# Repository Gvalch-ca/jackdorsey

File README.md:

# Lumberjerk keyboard by Gvalch'ca

The design is inspired by Lumberjack PCB. It is designed by peej and available at this repo:
https://github.com/peej/lumberjack-keyboard/

## About the PCB

Lumberjerk is designed for Alps SKCL/SKCM and NMB Hi-Tek 725 "Space Invaders" switches. It is a 6x5 "split" with exposed components in between the halves.

Form-factor of the PCB is standard 60% (GH60-compatible). Two middle posts are removed though (but who cares?). Also the posts between Tab & Q and ] & \ are partially covered with the switches and it might be difficult to screw them. If you use SI switches, you'll also need to remove one switch leg in order to use these posts.

The PCB is designed to be used with BLE pro-micro compatible controller (e.g. nice!nano). Wired controller could be used too. In this case you'll need to solder JST connector and USB mini B (bottom mount) and connect your controller to the internal JST.

Also, there is second JST connector on the bottom of the board. It is meant to be used with daughterboard. OFC it requires you to use the same method with internal USB->JST cable.

## Build guide
TBD

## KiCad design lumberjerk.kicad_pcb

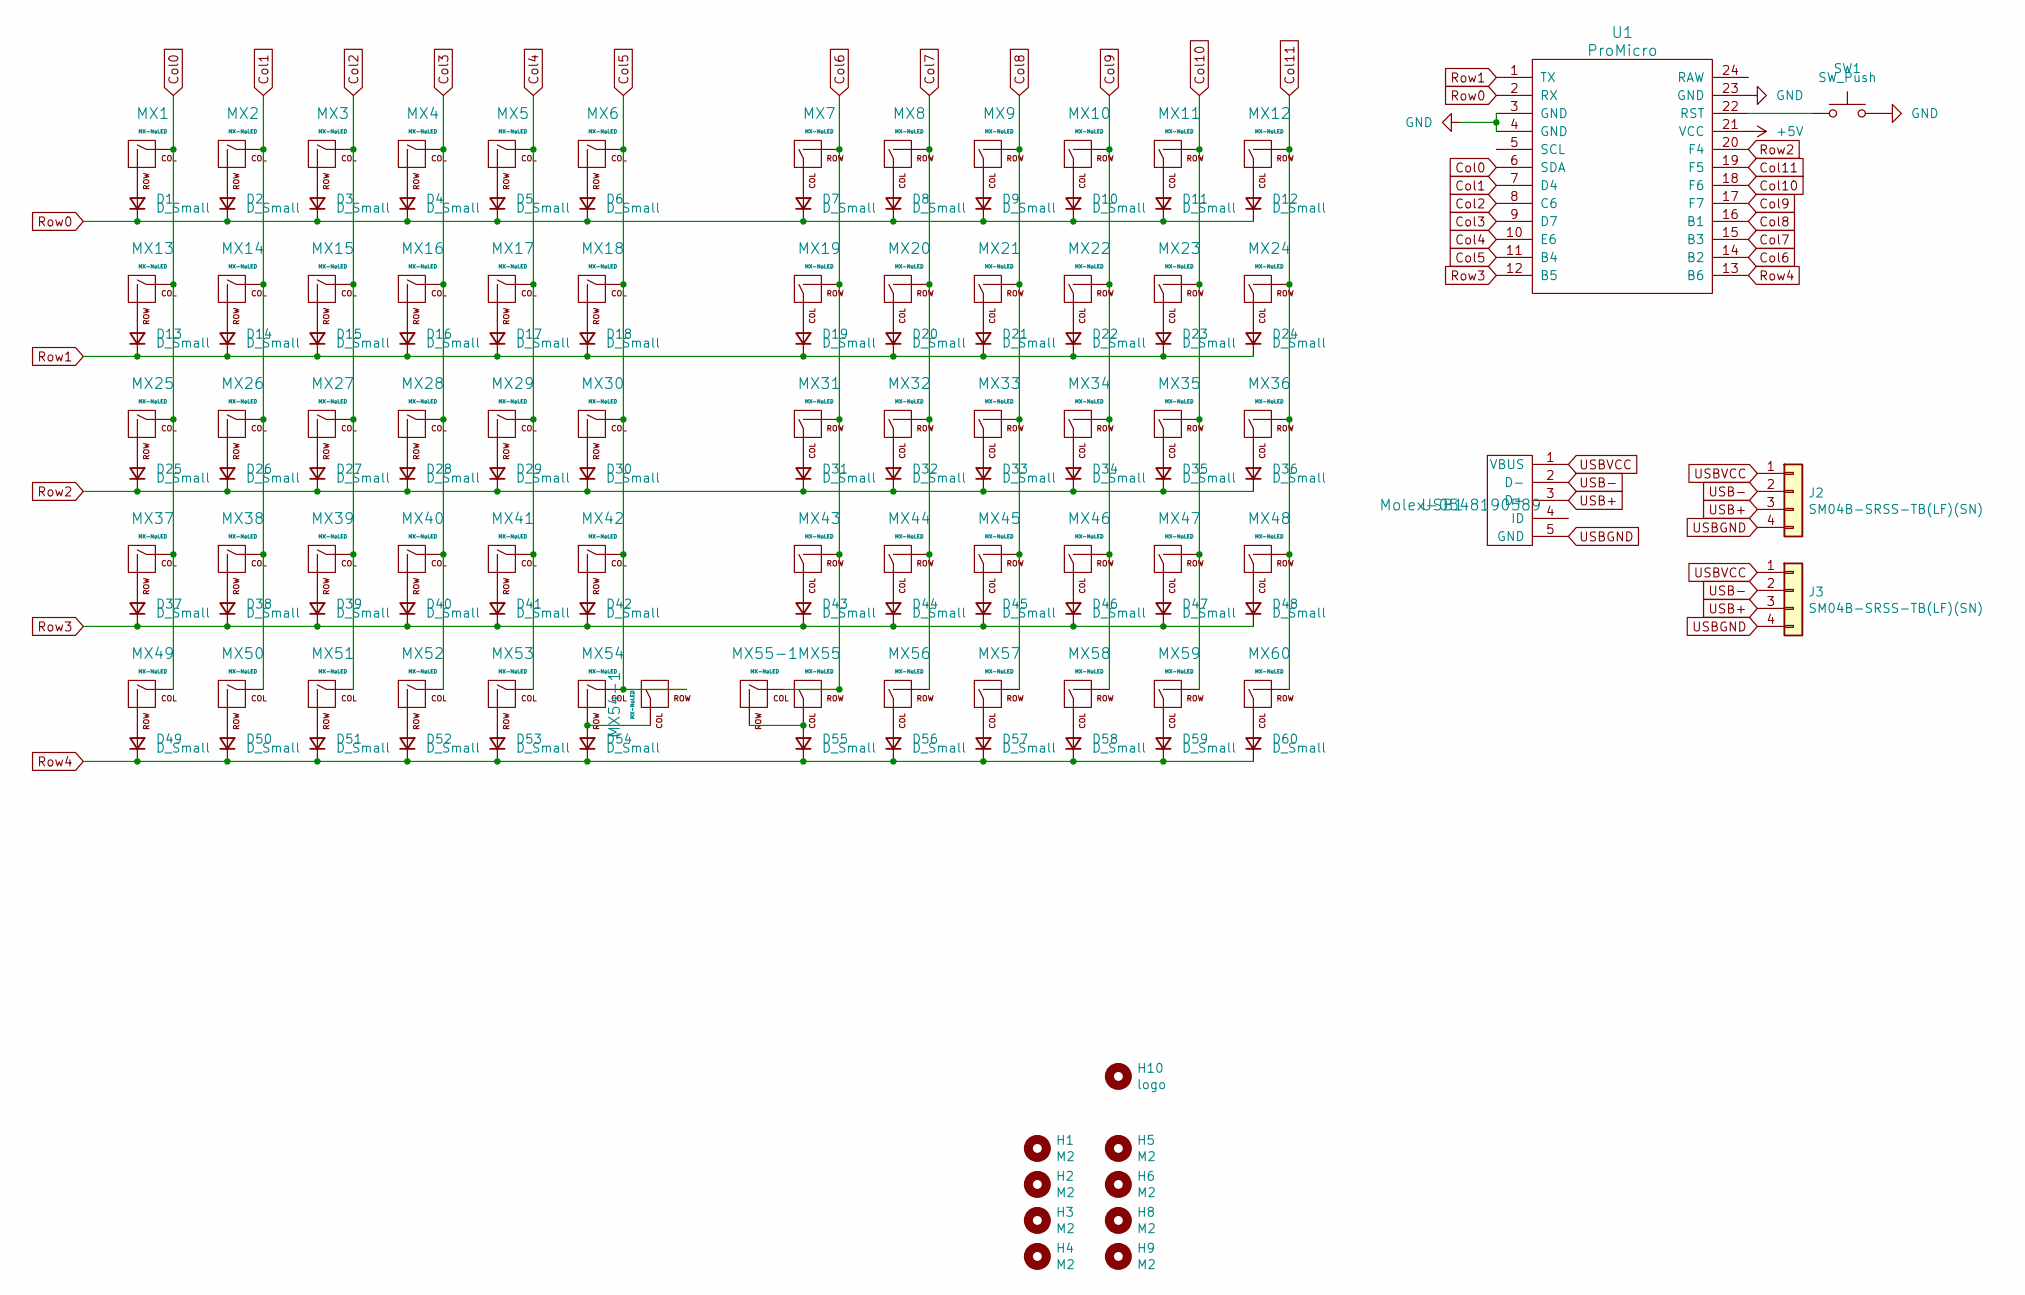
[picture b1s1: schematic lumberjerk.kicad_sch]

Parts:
D1, D2, D3, D4, D5, D6, D7, D8, D9, D10, D11, D12, D13, D14, D15, D16, D17, D18, D19, D20, D21, D22, D23, D24, D25, D26, D27, D28, D29, D30, D31, D32, D33, D34, D35, D36, D37, D38, D39, D40, D41, D42, D43, D44, D45, D46, D47, D48, D49, D50, D51, D52, D53, D54, D55, D56, D57, D58, D59, D60: D_Small; D_SOD-123
H1, H2, H3, H4: M2; MountingHole_M2
H5, H6: M2; poker-screw-wide
H8, H9: M2; poker-screw-normal
H10: logo; falcon
J2, J3: SM04B-SRSS-TB(LF)(SN); JST-SR-4; Manufacturer Part No SM04B-SRSS-TB(LF)(SN); LCSC Part No C160404
MX1, MX2, MX3, MX4, MX5, MX6, MX7, MX8, MX9, MX10, MX11, MX12, MX13, MX14, MX15, MX16, MX17, MX18, MX19, MX20, MX21, MX22, MX23, MX24, MX25, MX26, MX27, MX28, MX29, MX30, MX31, MX32, MX33, MX34, MX35, MX36, MX37, MX38, MX39, MX40, MX41, MX42, MX43, MX44, MX45, MX46, MX47, MX48, MX49, MX50, MX51, MX52, MX53, MX54, MX55, MX56, MX57, MX58, MX59, MX60: MX-NoLED; ALPS-SI-1U
MX54-1, MX55-1: MX-NoLED; ALPS-SI-2U
SW1: SW_Push; Jumper-UserFriendly
U1: ProMicro
USB1: Molex-0548190589; Molex-54819-0519-MFG

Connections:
+5V: U1.21 (VCC)
Col0: MX1.1 (COL), MX13.1 (COL), MX25.1 (COL), MX37.1 (COL), MX49.1 (COL), U1.6 (SDA)
Col1: MX2.1 (COL), MX14.1 (COL), MX26.1 (COL), MX38.1 (COL), MX50.1 (COL), U1.7 (D4)
Col2: MX3.1 (COL), MX15.1 (COL), MX27.1 (COL), MX39.1 (COL), MX51.1 (COL), U1.8 (C6)
Col3: MX4.1 (COL), MX16.1 (COL), MX28.1 (COL), MX40.1 (COL), MX52.1 (COL), U1.9 (D7)
Col4: MX5.1 (COL), MX17.1 (COL), MX29.1 (COL), MX41.1 (COL), MX53.1 (COL), U1.10 (E6)
Col5: MX6.1 (COL), MX18.1 (COL), MX30.1 (COL), MX42.1 (COL), MX54.1 (COL), MX54-1.2 (ROW), U1.11 (B4)
Col6: MX7.2 (ROW), MX19.2 (ROW), MX31.2 (ROW), MX43.2 (ROW), MX55.2 (ROW), MX55-1.1 (COL), U1.14 (B2)
Col7: MX8.2 (ROW), MX20.2 (ROW), MX32.2 (ROW), MX44.2 (ROW), MX56.2 (ROW), U1.15 (B3)
Col8: MX9.2 (ROW), MX21.2 (ROW), MX33.2 (ROW), MX45.2 (ROW), MX57.2 (ROW), U1.16 (B1)
Col9: MX10.2 (ROW), MX22.2 (ROW), MX34.2 (ROW), MX46.2 (ROW), MX58.2 (ROW), U1.17 (F7)
Col10: MX11.2 (ROW), MX23.2 (ROW), MX35.2 (ROW), MX47.2 (ROW), MX59.2 (ROW), U1.18 (F6)
Col11: MX12.2 (ROW), MX24.2 (ROW), MX36.2 (ROW), MX48.2 (ROW), MX60.2 (ROW), U1.19 (F5)
GND: SW1.2, U1.3 (GND), U1.4 (GND), U1.23 (GND)
unnamed: D1.2 (A), MX1.2 (ROW)
unnamed: D2.2 (A), MX2.2 (ROW)
unnamed: D3.2 (A), MX3.2 (ROW)
unnamed: D4.2 (A), MX4.2 (ROW)
unnamed: D5.2 (A), MX5.2 (ROW)
unnamed: D6.2 (A), MX6.2 (ROW)
unnamed: D7.2 (A), MX7.1 (COL)
unnamed: D8.2 (A), MX8.1 (COL)
unnamed: D9.2 (A), MX9.1 (COL)
unnamed: D10.2 (A), MX10.1 (COL)
unnamed: D11.2 (A), MX11.1 (COL)
unnamed: D12.2 (A), MX12.1 (COL)
unnamed: D13.2 (A), MX13.2 (ROW)
unnamed: D14.2 (A), MX14.2 (ROW)
unnamed: D15.2 (A), MX15.2 (ROW)
unnamed: D16.2 (A), MX16.2 (ROW)
unnamed: D17.2 (A), MX17.2 (ROW)
unnamed: D18.2 (A), MX18.2 (ROW)
unnamed: D19.2 (A), MX19.1 (COL)
unnamed: D20.2 (A), MX20.1 (COL)
unnamed: D21.2 (A), MX21.1 (COL)
unnamed: D22.2 (A), MX22.1 (COL)
unnamed: D23.2 (A), MX23.1 (COL)
unnamed: D24.2 (A), MX24.1 (COL)
unnamed: D25.2 (A), MX25.2 (ROW)
unnamed: D26.2 (A), MX26.2 (ROW)
unnamed: D27.2 (A), MX27.2 (ROW)
unnamed: D28.2 (A), MX28.2 (ROW)
unnamed: D29.2 (A), MX29.2 (ROW)
unnamed: D30.2 (A), MX30.2 (ROW)
unnamed: D31.2 (A), MX31.1 (COL)
unnamed: D32.2 (A), MX32.1 (COL)
unnamed: D33.2 (A), MX33.1 (COL)
unnamed: D34.2 (A), MX34.1 (COL)
unnamed: D35.2 (A), MX35.1 (COL)
unnamed: D36.2 (A), MX36.1 (COL)
unnamed: D37.2 (A), MX37.2 (ROW)
unnamed: D38.2 (A), MX38.2 (ROW)
unnamed: D39.2 (A), MX39.2 (ROW)
unnamed: D40.2 (A), MX40.2 (ROW)
unnamed: D41.2 (A), MX41.2 (ROW)
unnamed: D42.2 (A), MX42.2 (ROW)
unnamed: D43.2 (A), MX43.1 (COL)
unnamed: D44.2 (A), MX44.1 (COL)
unnamed: D45.2 (A), MX45.1 (COL)
unnamed: D46.2 (A), MX46.1 (COL)
unnamed: D47.2 (A), MX47.1 (COL)
unnamed: D48.2 (A), MX48.1 (COL)
unnamed: D49.2 (A), MX49.2 (ROW)
unnamed: D50.2 (A), MX50.2 (ROW)
unnamed: D51.2 (A), MX51.2 (ROW)
unnamed: D52.2 (A), MX52.2 (ROW)
unnamed: D53.2 (A), MX53.2 (ROW)
unnamed: D54.2 (A), MX54.2 (ROW), MX54-1.1 (COL)
unnamed: D55.2 (A), MX55.1 (COL), MX55-1.2 (ROW)
unnamed: D56.2 (A), MX56.1 (COL)
unnamed: D57.2 (A), MX57.1 (COL)
unnamed: D58.2 (A), MX58.1 (COL)
unnamed: D59.2 (A), MX59.1 (COL)
unnamed: D60.2 (A), MX60.1 (COL)
unnamed: SW1.1, U1.22 (RST)
Row0: D1.1 (K), D2.1 (K), D3.1 (K), D4.1 (K), D5.1 (K), D6.1 (K), D7.1 (K), D8.1 (K), D9.1 (K), D10.1 (K), D11.1 (K), D12.1 (K), U1.2 (RX)
Row1: D13.1 (K), D14.1 (K), D15.1 (K), D16.1 (K), D17.1 (K), D18.1 (K), D19.1 (K), D20.1 (K), D21.1 (K), D22.1 (K), D23.1 (K), D24.1 (K), U1.1 (TX)
Row2: D25.1 (K), D26.1 (K), D27.1 (K), D28.1 (K), D29.1 (K), D30.1 (K), D31.1 (K), D32.1 (K), D33.1 (K), D34.1 (K), D35.1 (K), D36.1 (K), U1.20 (F4)
Row3: D37.1 (K), D38.1 (K), D39.1 (K), D40.1 (K), D41.1 (K), D42.1 (K), D43.1 (K), D44.1 (K), D45.1 (K), D46.1 (K), D47.1 (K), D48.1 (K), U1.12 (B5)
Row4: D49.1 (K), D50.1 (K), D51.1 (K), D52.1 (K), D53.1 (K), D54.1 (K), D55.1 (K), D56.1 (K), D57.1 (K), D58.1 (K), D59.1 (K), D60.1 (K), U1.13 (B6)
USB+: J2.3, J3.3, USB1.3 (D+)
USB-: J2.2, J3.2, USB1.2 (D-)
USBGND: J2.4, J3.4, USB1.5 (GND)
USBVCC: J2.1, J3.1, USB1.1 (VBUS)

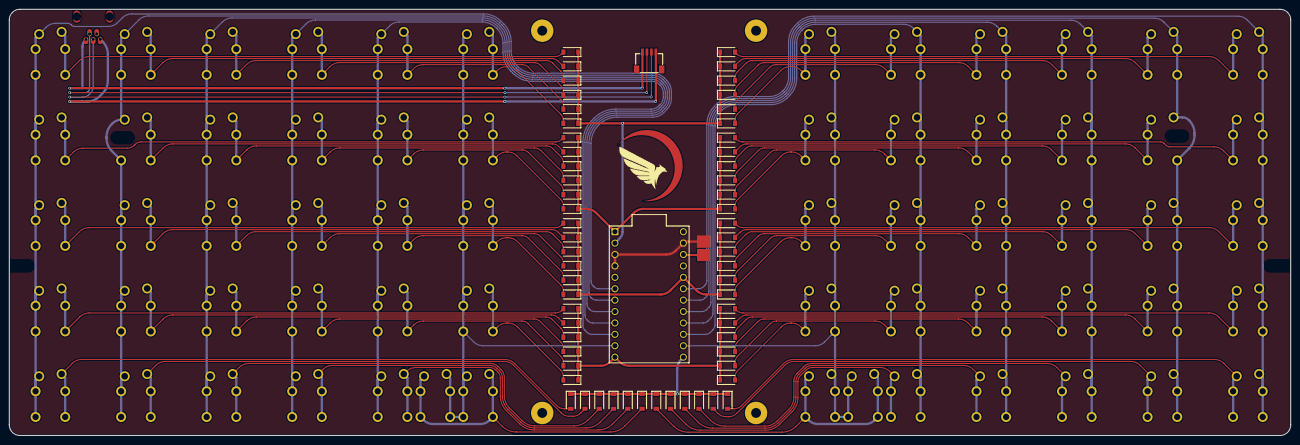
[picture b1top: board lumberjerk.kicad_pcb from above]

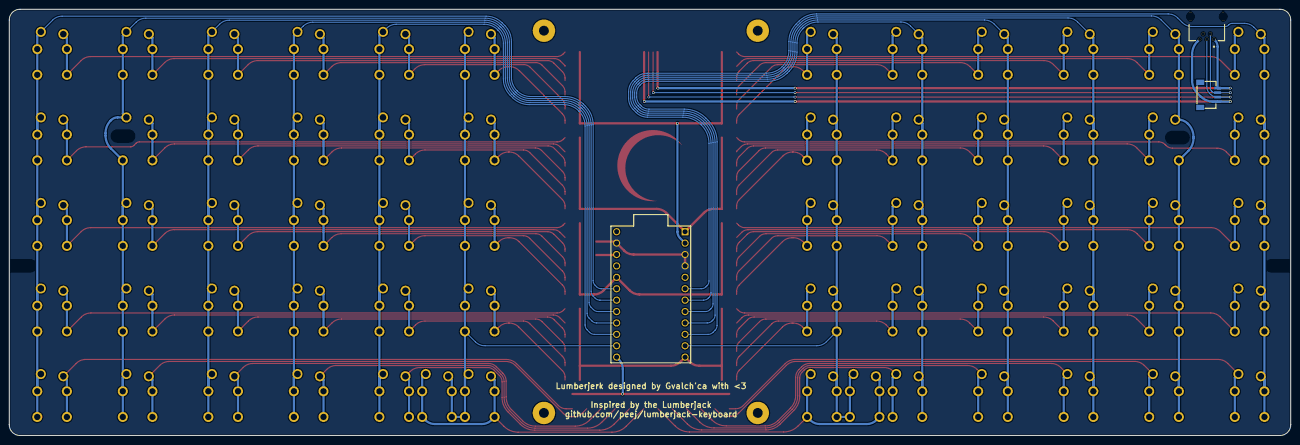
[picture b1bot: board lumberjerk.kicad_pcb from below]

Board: 2 copper layers, 285.4 x 94.9 mm, 136 parts (2 on the bottom side), 83 nets.

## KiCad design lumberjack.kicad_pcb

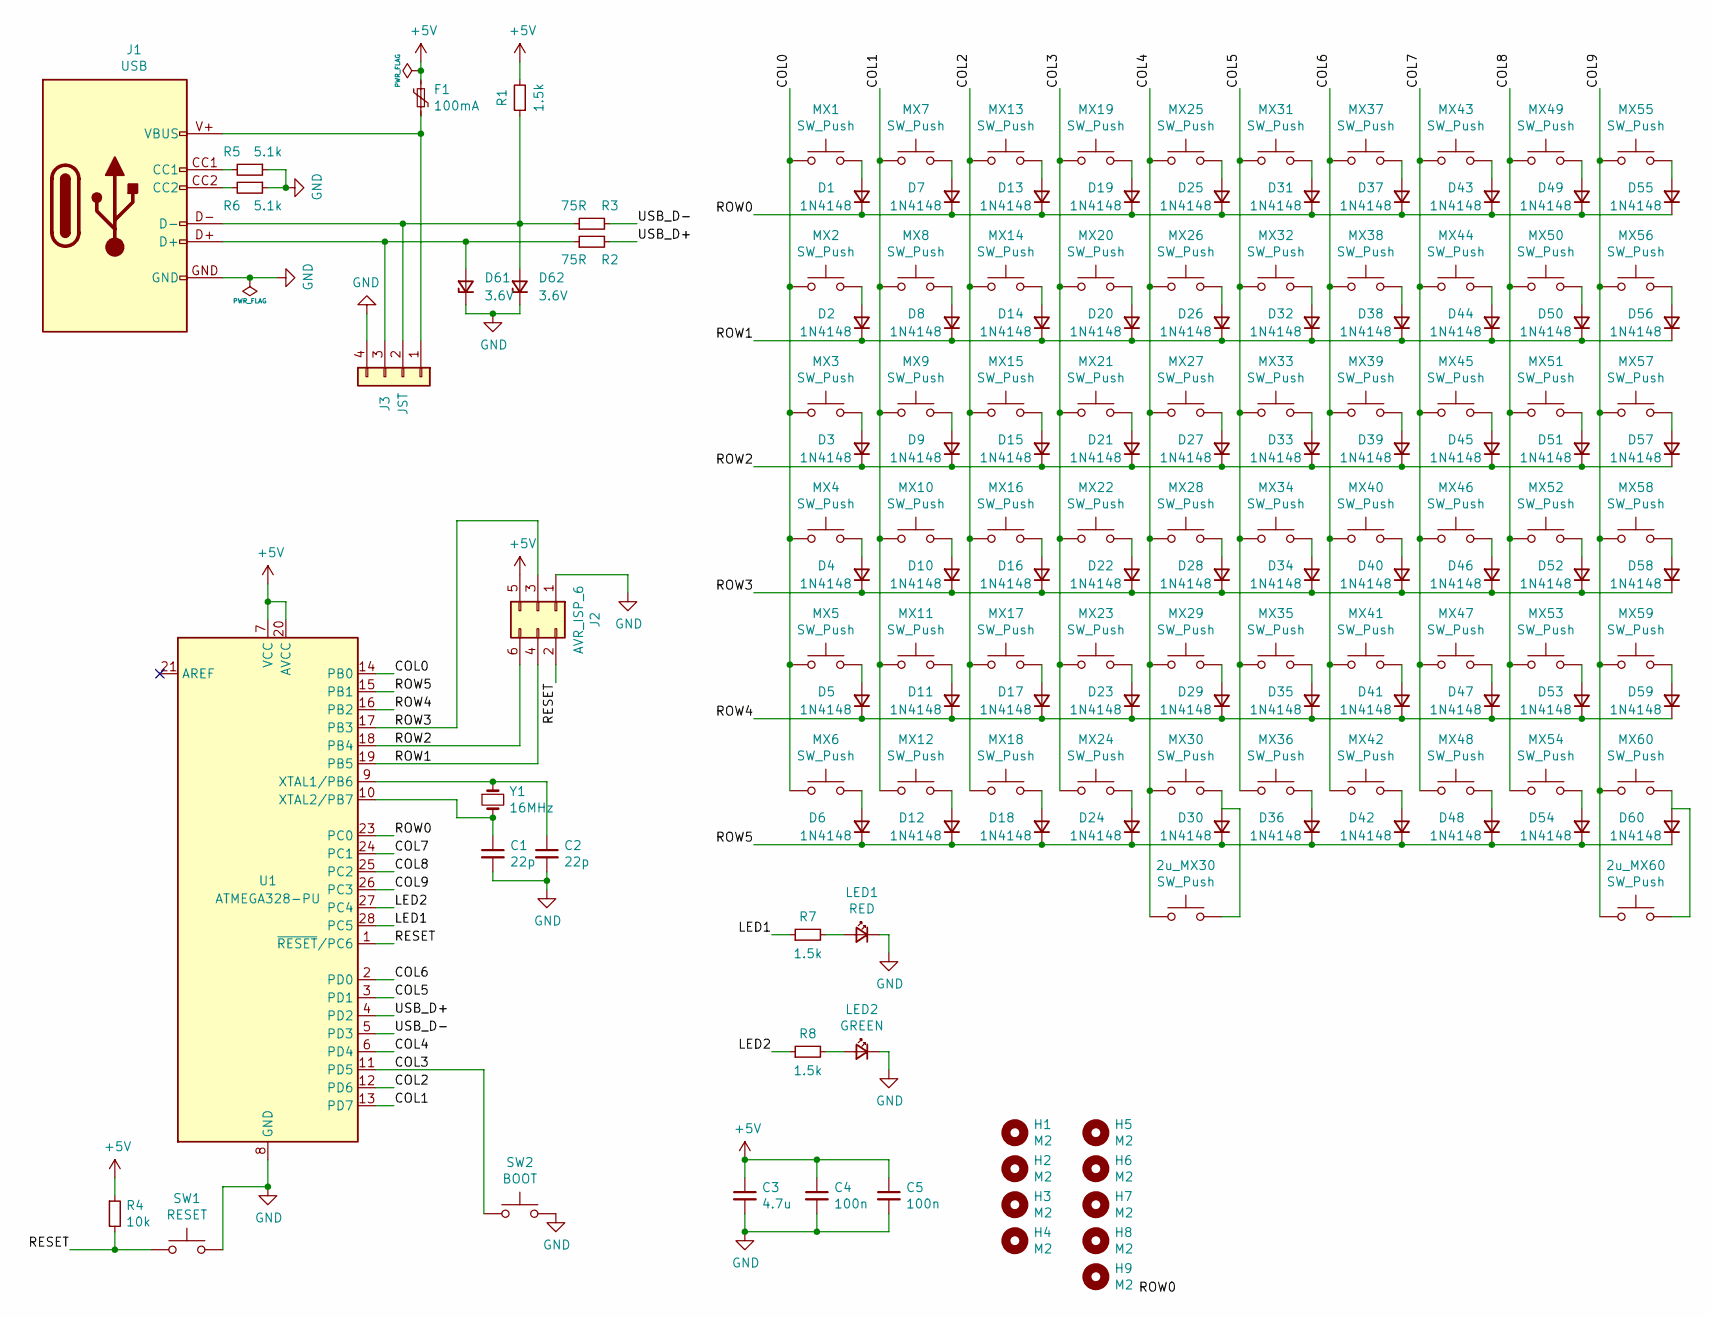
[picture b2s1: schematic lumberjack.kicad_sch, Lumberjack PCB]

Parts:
2u_MX30, 2u_MX60: SW_Push; MX_PCB_200B
C1, C2: 22p; C_Disc_D3.0mm_W1.6mm_P2.50mm
C3: 4.7u; CP_Radial_D4.0mm_P1.50mm
C4, C5: 100n; C_Disc_D4.3mm_W1.9mm_P5.00mm
D1, D2, D3, D4, D5, D6, D7, D8, D9, D10, D11, D12, D13, D14, D15, D16, D17, D18, D19, D20, D21, D22, D23, D24, D25, D26, D27, D28, D29, D30, D31, D32, D33, D34, D35, D36, D37, D38, D39, D40, D41, D42, D43, D44, D45, D46, D47, D48, D49, D50, D51, D52, D53, D54, D55, D56, D57, D58, D59, D60: 1N4148; D_DO-35_SOD27_P7.62mm_Horizontal
D61, D62: 3.6V; D_DO-35_SOD27_P7.62mm_Horizontal
F1: 100mA; Fuse_Bourns_MF-RHT100
H1, H2, H3, H4: M2; MountingHole_M2
H5, H6: M2; poker-screw-wide
H7, H8, H9: M2; poker-screw-normal
J1: USB; USB_Hybrid_THT
J2: AVR_ISP_6; PinHeader_2x03_P2.54mm_Vertical
J3: JST; JST_SH_SM04B-SRSS-TB_1x04-1MP_P1.00mm_Horizontal
LED1: RED; LED_D3.0mm
LED2: GREEN; LED_D3.0mm
MX1: SW_Push; ALPS-SI-1U
MX2, MX3, MX4, MX5, MX6, MX7, MX9, MX10, MX11, MX12, MX13, MX14, MX15, MX16, MX17, MX18, MX19, MX20, MX21, MX22, MX23, MX24, MX25, MX26, MX27, MX28, MX29, MX30, MX31, MX32, MX33, MX34, MX35, MX36, MX37, MX39, MX40, MX41, MX42, MX43, MX44, MX45, MX46, MX47, MX48, MX49, MX50, MX51, MX52, MX53, MX54, MX55, MX56, MX57, MX58, MX59, MX60: SW_Push; MX
MX8: SW_Push; ALPS-SI-deleted-left-pin-1U
MX38: SW_Push; ALPS-SI-deleted-right-pin-1U
R1, R7, R8: 1.5k; R_Axial_DIN0204_L3.6mm_D1.6mm_P7.62mm_Horizontal
R2, R3: 75R; R_Axial_DIN0204_L3.6mm_D1.6mm_P7.62mm_Horizontal
R4: 10k; R_Axial_DIN0204_L3.6mm_D1.6mm_P7.62mm_Horizontal
R5, R6: 5.1k; R_Axial_DIN0204_L3.6mm_D1.6mm_P7.62mm_Horizontal
SW1: RESET; SW_PUSH_6mm
SW2: BOOT; SW_PUSH_6mm
U1: ATMEGA328-PU; DIP-28_W7.62mm
Y1: 16MHz; Crystal_HC49-4H_Vertical

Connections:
+5V: C3.1, C4.1, C5.1, F1.2, J2.5, R1.2, R4.1, U1.7 (VCC), U1.20 (AVCC)
/COL0: MX1.2, MX2.2, MX3.2, MX4.2, MX5.2, MX6.2, U1.14 (PB0)
/COL1: MX7.2, MX8.2, MX9.2, MX10.2, MX11.2, MX12.2, U1.13 (PD7)
/COL2: MX13.2, MX14.2, MX15.2, MX16.2, MX17.2, MX18.2, U1.12 (PD6)
/COL3: MX19.2, MX20.2, MX21.2, MX22.2, MX23.2, MX24.2, SW2.1, U1.11 (PD5)
/COL4: 2u_MX30.2, MX25.2, MX26.2, MX27.2, MX28.2, MX29.2, MX30.2, U1.6 (PD4)
/COL5: MX31.2, MX32.2, MX33.2, MX34.2, MX35.2, MX36.2, U1.3 (PD1)
/COL6: MX37.2, MX38.2, MX39.2, MX40.2, MX41.2, MX42.2, U1.2 (PD0)
/COL7: MX43.2, MX44.2, MX45.2, MX46.2, MX47.2, MX48.2, U1.24 (PC1)
/COL8: MX49.2, MX50.2, MX51.2, MX52.2, MX53.2, MX54.2, U1.25 (PC2)
/COL9: 2u_MX60.2, MX55.2, MX56.2, MX57.2, MX58.2, MX59.2, MX60.2, U1.26 (PC3)
/LED1: R7.1, U1.28 (PC5)
/LED2: R8.1, U1.27 (PC4)
/RESET: J2.2, R4.2, SW1.1, U1.1 (~RESET/PC6)
/ROW0: D1.1 (K), D7.1 (K), D13.1 (K), D19.1 (K), D25.1 (K), D31.1 (K), D37.1 (K), D43.1 (K), D49.1 (K), D55.1 (K), U1.23 (PC0)
/ROW1: D2.1 (K), D8.1 (K), D14.1 (K), D20.1 (K), D26.1 (K), D32.1 (K), D38.1 (K), D44.1 (K), D50.1 (K), D56.1 (K), J2.4, U1.19 (PB5)
/ROW2: D3.1 (K), D9.1 (K), D15.1 (K), D21.1 (K), D27.1 (K), D33.1 (K), D39.1 (K), D45.1 (K), D51.1 (K), D57.1 (K), J2.6, U1.18 (PB4)
/ROW3: D4.1 (K), D10.1 (K), D16.1 (K), D22.1 (K), D28.1 (K), D34.1 (K), D40.1 (K), D46.1 (K), D52.1 (K), D58.1 (K), J2.3, U1.17 (PB3)
/ROW4: D5.1 (K), D11.1 (K), D17.1 (K), D23.1 (K), D29.1 (K), D35.1 (K), D41.1 (K), D47.1 (K), D53.1 (K), D59.1 (K), U1.16 (PB2)
/ROW5: D6.1 (K), D12.1 (K), D18.1 (K), D24.1 (K), D30.1 (K), D36.1 (K), D42.1 (K), D48.1 (K), D54.1 (K), D60.1 (K), U1.15 (PB1)
/USB_D+: R2.2, U1.4 (PD2)
/USB_D-: R3.2, U1.5 (PD3)
unnamed: 2u_MX30.1, D30.2 (A), MX30.1
unnamed: 2u_MX60.1, D60.2 (A), MX60.1
unnamed: C1.1, U1.10 (XTAL2/PB7), Y1.2
unnamed: C2.1, U1.9 (XTAL1/PB6), Y1.1
unnamed: D1.2 (A), MX1.1
unnamed: D2.2 (A), MX2.1
unnamed: D3.2 (A), MX3.1
unnamed: D4.2 (A), MX4.1
unnamed: D5.2 (A), MX5.1
unnamed: D6.2 (A), MX6.1
unnamed: D7.2 (A), MX7.1
unnamed: D8.2 (A), MX8.1
unnamed: D9.2 (A), MX9.1
unnamed: D10.2 (A), MX10.1
unnamed: D11.2 (A), MX11.1
unnamed: D12.2 (A), MX12.1
unnamed: D13.2 (A), MX13.1
unnamed: D14.2 (A), MX14.1
unnamed: D15.2 (A), MX15.1
unnamed: D16.2 (A), MX16.1
unnamed: D17.2 (A), MX17.1
unnamed: D18.2 (A), MX18.1
unnamed: D19.2 (A), MX19.1
unnamed: D20.2 (A), MX20.1
unnamed: D21.2 (A), MX21.1
unnamed: D22.2 (A), MX22.1
unnamed: D23.2 (A), MX23.1
unnamed: D24.2 (A), MX24.1
unnamed: D25.2 (A), MX25.1
unnamed: D26.2 (A), MX26.1
unnamed: D27.2 (A), MX27.1
unnamed: D28.2 (A), MX28.1
unnamed: D29.2 (A), MX29.1
unnamed: D31.2 (A), MX31.1
unnamed: D32.2 (A), MX32.1
unnamed: D33.2 (A), MX33.1
unnamed: D34.2 (A), MX34.1
unnamed: D35.2 (A), MX35.1
unnamed: D36.2 (A), MX36.1
unnamed: D37.2 (A), MX37.1
unnamed: D38.2 (A), MX38.1
unnamed: D39.2 (A), MX39.1
unnamed: D40.2 (A), MX40.1
unnamed: D41.2 (A), MX41.1
unnamed: D42.2 (A), MX42.1
unnamed: D43.2 (A), MX43.1
unnamed: D44.2 (A), MX44.1
unnamed: D45.2 (A), MX45.1
unnamed: D46.2 (A), MX46.1
unnamed: D47.2 (A), MX47.1
unnamed: D48.2 (A), MX48.1
unnamed: D49.2 (A), MX49.1
unnamed: D50.2 (A), MX50.1
unnamed: D51.2 (A), MX51.1
unnamed: D52.2 (A), MX52.1
unnamed: D53.2 (A), MX53.1
unnamed: D54.2 (A), MX54.1
unnamed: D55.2 (A), MX55.1
unnamed: D56.2 (A), MX56.1
unnamed: D57.2 (A), MX57.1
unnamed: D58.2 (A), MX58.1
unnamed: D59.2 (A), MX59.1
unnamed: F1.1, J1.V+ (VBUS), J3.1
unnamed: J1.CC1, R5.2
unnamed: J1.CC2, R6.2
unnamed: LED1.2 (A), R7.2
unnamed: LED2.2 (A), R8.2

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
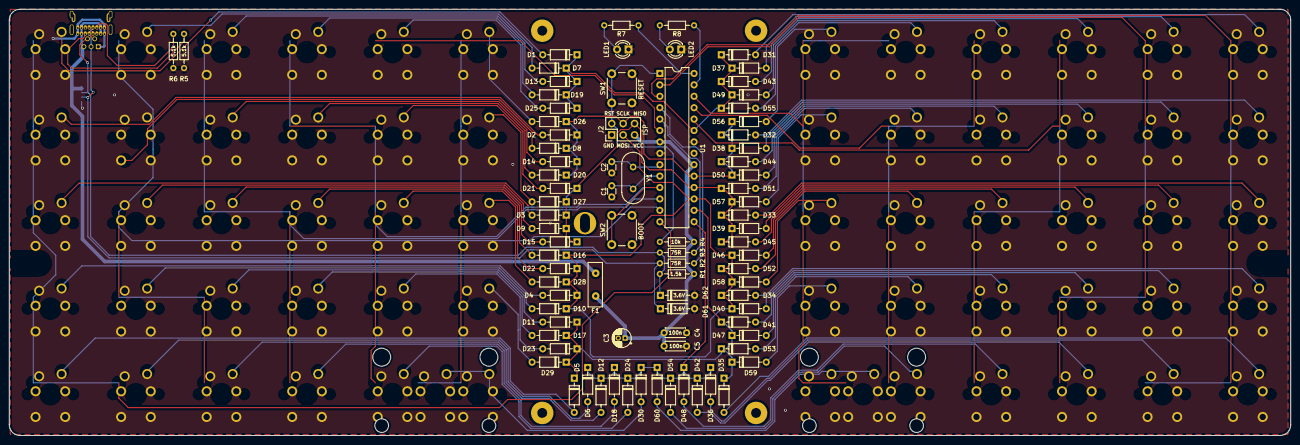
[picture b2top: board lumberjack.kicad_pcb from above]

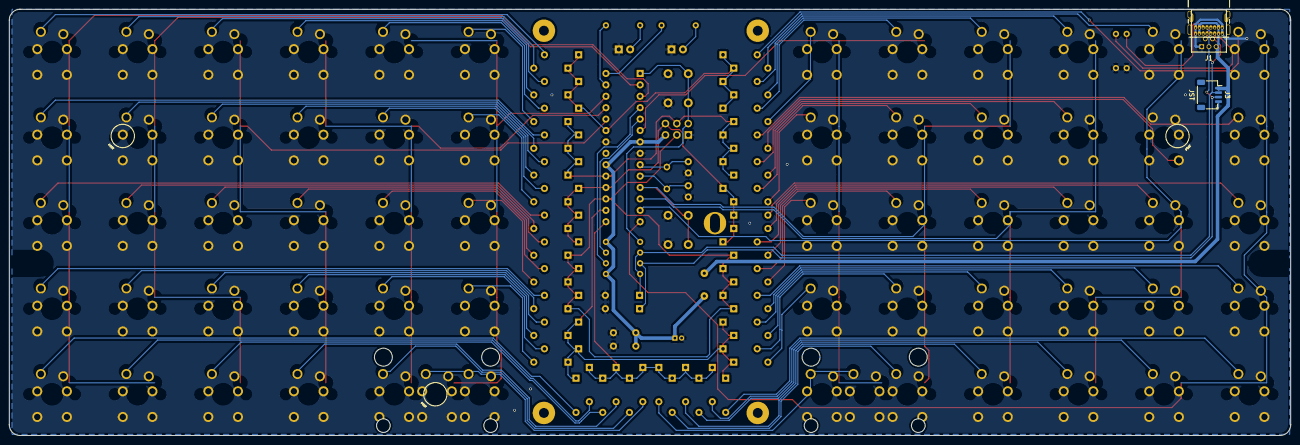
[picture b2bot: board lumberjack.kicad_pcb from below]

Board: 2 copper layers, 285.4 x 94.9 mm, 154 parts (2 on the bottom side), 92 nets.

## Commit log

2021-10-09 Init
2021-10-09 Add submodule
2021-10-09 1st ver of routing
2022-04-27 Remake from scratch
2022-04-28 Finalize design, add gerbers
